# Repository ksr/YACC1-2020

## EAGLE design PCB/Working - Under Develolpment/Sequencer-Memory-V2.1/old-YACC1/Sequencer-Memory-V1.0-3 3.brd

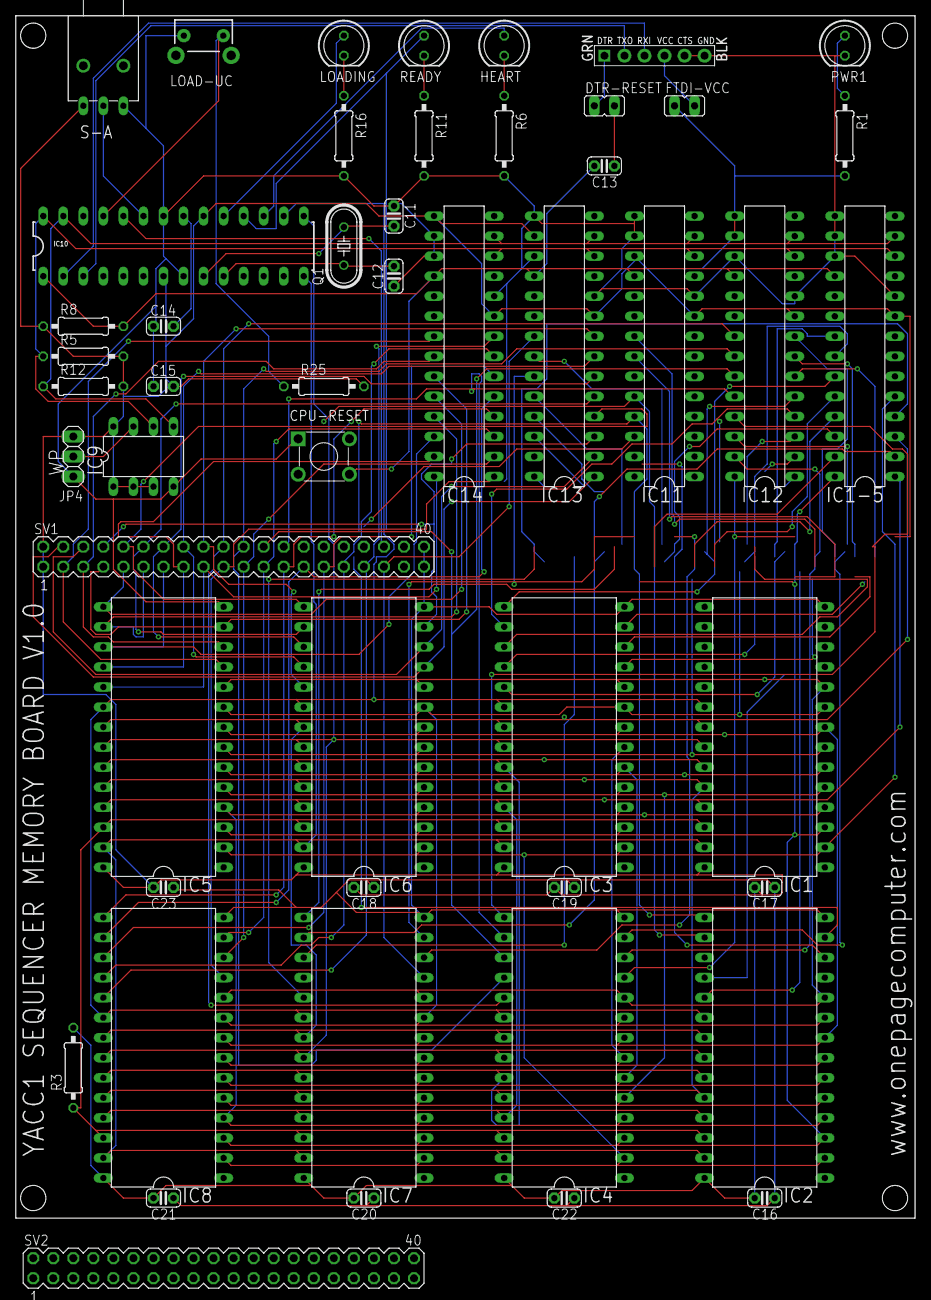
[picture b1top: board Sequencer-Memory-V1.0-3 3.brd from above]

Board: 2 copper layers, 114.0 x 152.4 mm, 51 parts (0 on the bottom side), 93 nets.

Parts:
C11, C12: 20pf; C025-024X044
C13, C14, C15, C16, C17, C18, C19, C20, C21, C22, C23: 0.1; C025-024X044
CPU-RESET: TS-1109-7; SW4-6.2X6.2X5.0MM
DTR-RESET: JP1
FTDI-VCC: JP1
HEART: LED5MM
IC1, IC2, IC3, IC4, IC5, IC6, IC7, IC8: DIL28-6
IC1-5, IC11, IC12, IC13, IC14: MCP23017SP; DIL28-3
IC9: 24AA01P; DIL8
IC10: ATMEGA328P_PDIP; DIL28-3
JP3: FTDI_DEVICE; FTDI_DEVICE_SIDE
JP4: 1X03
LOAD-UC: SWITCH-MOMENTARY-2SIDE_EZ; TACTILE-PTH-SIDEEZ
LOADING: LED5MM
PWR1: LED5MM
Q1: 16Mhz; HC49/S
R1, R6, R11, R16: 330; 0207/10
R3, R8, R25: 10k; 0207/10
R5, R12: 2.2k; 0207/10
READY: LED5MM
S-A: 9070-1W
SV1, SV2: MA20-2

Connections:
-CMEMRD: IC1.22, IC2.22, IC3.22, IC4.22, IC5.22, IC6.22, IC7.22, IC8.22, IC10.15
-CMEMSEL: IC1.20, IC2.20, IC3.20, IC4.20, IC5.20, IC6.20, IC7.20, IC8.20, IC10.16
-CMEMWR: IC1.27, IC2.27, IC3.27, IC4.27, IC5.27, IC6.27, IC7.27, IC8.27, IC10.14
-RESET: C13.2, CPU-RESET.3, IC1-5.18, IC10.1, IC11.18, IC12.18, IC13.18, IC14.18, R8.2
AC-LD: IC3.17, IC12.3, SV2.15
AC-LD-INV: IC3.18, IC12.2, SV2.13
AC-RD: IC3.16, IC12.4, SV2.17
ADDR-REG-ID0: IC5.12, IC14.22, SV1.5
ADDR-REG-ID1: IC5.13, IC14.23, SV1.7
ADDR-REG-LD: IC5.15, IC14.24, SV1.9
ADDR-REG-RD: IC5.16, IC14.25, SV1.11
ALU0: IC4.13, IC12.26, SV2.5
ALU1: IC4.12, IC12.27, SV2.7
ALU2: IC4.11, IC12.28, SV2.9
ALU3: IC3.19, IC12.1, SV2.11
ALU-FUNC: IC4.15, IC12.25, SV2.3
ARD-RXIN: IC10.2, JP3.P$3
ARD-TXOUT: IC10.3, JP3.P$2
BR-COND: IC3.13, IC12.6, SV2.4
CADDR0: IC1.10, IC1-5.21, IC2.10, IC3.10, IC4.10, IC5.10, IC6.10, IC7.10, IC8.10, SV2.14
CADDR1: IC1.9, IC1-5.22, IC2.9, IC3.9, IC4.9, IC5.9, IC6.9, IC7.9, IC8.9, SV2.16
CADDR2: IC1.8, IC1-5.23, IC2.8, IC3.8, IC4.8, IC5.8, IC6.8, IC7.8, IC8.8, SV2.18
CADDR3: IC1.7, IC1-5.24, IC2.7, IC3.7, IC4.7, IC5.7, IC6.7, IC7.7, IC8.7, SV2.20
CADDR4: IC1.6, IC1-5.25, IC2.6, IC3.6, IC4.6, IC5.6, IC6.6, IC7.6, IC8.6, SV2.22
CADDR5: IC1.5, IC1-5.26, IC2.5, IC3.5, IC4.5, IC5.5, IC6.5, IC7.5, IC8.5, SV2.24
CADDR6: IC1.4, IC1-5.27, IC2.4, IC3.4, IC4.4, IC5.4, IC6.4, IC7.4, IC8.4, SV2.26
CADDR7: IC1.3, IC1-5.28, IC2.3, IC3.3, IC4.3, IC5.3, IC6.3, IC7.3, IC8.3, SV2.28
CADDR8: IC1.25, IC1-5.1, IC2.25, IC3.25, IC4.25, IC5.25, IC6.25, IC7.25, IC8.25, SV2.30
CADDR9: IC1.24, IC1-5.2, IC2.24, IC3.24, IC4.24, IC5.24, IC6.24, IC7.24, IC8.24, SV2.32
CADDR10: IC1.21, IC1-5.3, IC2.21, IC3.21, IC4.21, IC5.21, IC6.21, IC7.21, IC8.21, SV2.34
CADDR11: IC1.23, IC1-5.4, IC2.23, IC3.23, IC4.23, IC5.23, IC6.23, IC7.23, IC8.23, SV2.36
CADDR12: IC1.2, IC1-5.5, IC2.2, IC3.2, IC4.2, IC5.2, IC6.2, IC7.2, IC8.2, SV2.38
CMEMSEL: IC1.26, IC2.26, IC3.26, IC4.26, IC5.26, IC6.26, IC7.26, IC8.26, R3.1
GND: C11.1, C12.1, C14.1, C15.1, C16.1, C17.1, C18.1, C19.1, C20.1, C21.1, C22.1, C23.1, CPU-RESET.1, IC1.14, IC1-5.10, IC1-5.15, IC1-5.16, IC1-5.17, IC2.14, IC3.14, IC4.14, IC5.14, IC6.14, IC7.14, IC8.14, IC9.4, IC10.8, IC10.22, IC11.10, IC11.15, IC11.16, IC12.10, IC12.17, IC13.10, IC13.15, IC13.17, IC14.10, IC14.16, IC14.17, JP3.P$5, JP3.P$6, JP4.1, LOAD-UC.2, PWR1.K, R6.2, R11.2, R16.2, S-A.3, SV1.39, SV1.40, SV2.39, SV2.40
H/L-SWAP: IC3.12, IC12.7, SV2.6
HEART: HEART.A, IC10.17
I/D-REG-DN: IC6.13, IC13.3, SV1.8
I/D-REG-LD: IC6.11, IC13.1, SV1.4
I/D-REG-RD: IC6.12, IC13.2, SV1.6
I/D-REG-UP: IC6.15, IC13.4, SV1.10
I/O-ADDR: IC7.17, IC13.26, SV2.29
I/O-RD: IC7.16, IC13.25, SV2.27
I/O-WR: IC7.15, IC13.24, SV2.25
INT-EN: IC2.15, IC11.25, SV1.32
INT-START: IC2.16, IC11.24, SV1.30
INTA: IC7.19, IC13.28, SV2.33
LD: IC10.19, LOADING.A
LD-INS-REG: IC2.13, IC11.26, SV2.35
MEM-RD: IC7.13, IC13.23, SV2.23
MEM-WR: IC7.12, IC13.22, SV2.21
unnamed: PWR1.A, R1.1
unnamed: C11.2, IC10.9, Q1.2
unnamed: C12.2, IC10.10, Q1.1
unnamed: C13.1, DTR-RESET.2
unnamed: C14.2, IC10.21
unnamed: R11.1, READY.K
unnamed: LOADING.K, R16.1
unnamed: HEART.K, R6.1
unnamed: IC10.23, S-A.2
unnamed: IC9.7, JP4.2
unnamed: DTR-RESET.1, JP3.P$1
unnamed: FTDI-VCC.2, JP3.P$4
unnamed: IC10.25, LOAD-UC.1, R25.1
OUT-OFF: IC2.19, IC11.21, SV2.10
OUT-ON: IC3.11, IC12.8, SV2.8
READY: IC10.18, READY.A, SV1.36
REG-BRD-LD-ID0: IC8.12, IC14.2, SV1.21
REG-BRD-LD-ID1: IC8.13, IC14.3, SV1.23
REG-BRD-RD-ID0: IC5.17, IC14.26, SV1.13
REG-BRD-RD-ID1: IC5.18, IC14.27, SV1.15
REG-FUNC: IC5.11, IC14.21, SV1.3
REG-LD-HI: IC7.11, IC13.21, SV1.35
REG-LD-ID0: IC8.15, IC14.4, SV1.25
REG-LD-ID1: IC8.16, IC14.5, SV1.27
REG-LD-LO: IC8.18, IC14.7, SV1.31
REG-RD-HI: IC8.19, IC14.8, SV1.33
REG-RD-ID0: IC5.19, IC14.28, SV1.17
REG-RD-ID1: IC8.11, IC14.1, SV1.19
REG-RD-LO: IC8.17, IC14.6, SV1.29
RESET: IC2.18, IC11.22, SV2.12
SCL: IC1-5.12, IC9.6, IC10.28, IC11.12, IC12.12, IC13.12, IC14.12, R5.1
SDA: IC1-5.13, IC9.5, IC10.27, IC11.13, IC12.13, IC13.13, IC14.13, R12.1
SP/PC-ADDR-RD: IC6.19, IC13.8, SV1.18
SP/PC-DATA-RD-HI: IC6.18, IC13.7, SV1.16
SP/PC-DATA-RD-LO: IC6.17, IC13.6, SV1.14
SP/PC-DN: IC4.17, IC12.23, SV1.24
SP/PC-LD-HI: IC4.18, IC12.22, SV1.22
SP/PC-LD-LO: IC4.19, IC12.21, SV1.20
SP/PC-SEL: IC6.16, IC13.5, SV1.12
SP/PC-UP: IC4.16, IC12.24, SV1.26
SR-LD: IC3.15, IC12.5, SV2.19
UCODE-COUNT-RESET: IC2.12, IC11.27, SV2.37
VCC: C15.2, C16.2, C17.2, C18.2, C19.2, C20.2, C21.2, C22.2, C23.2, FTDI-VCC.1, IC1.28, IC1-5.9, IC2.28, IC3.28, IC4.28, IC5.28, IC6.28, IC7.28, IC8.28, IC9.1, IC9.2, IC9.3, IC9.8, IC10.7, IC10.20, IC11.9, IC11.17, IC12.9, IC12.15, IC12.16, IC13.9, IC13.16, IC14.9, IC14.15, JP4.3, R1.2, R3.2, R5.2, R8.1, R12.2, R25.2, S-A.1, SV1.1, SV1.2, SV2.1, SV2.2

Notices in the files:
parts and their libraries:
SparkFun-DigitalIC: Licensing: CC v3.0 Share-Alike You are welcome to use this library for commercial purposes.
